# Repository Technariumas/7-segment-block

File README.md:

# 7-segment-block

A big 7 segment plug and play module designed to be easily chainable and be driven by SPI bus.

```Arduino
#include<SPI.h>
#include <Bounce2.h>

#define ZERO  0b11101110
#define ONE   0b10000010
#define TWO   0b11011100
#define THREE 0b11010110
#define FOUR  0b10110010
#define FIVE  0b01110110
#define SIX   0b01111110
#define SEVEN 0b11000010
#define EIGHT 0b11111110
#define NINE  0b11110110
#define DARK  0b00000000

uint8_t digits[] = {ZERO, ONE, TWO, THREE, FOUR, FIVE, SIX, SEVEN, EIGHT, NINE, DARK};
uint8_t brightness = 0;

void setup() {
  Serial.begin(9600);
  randomSeed(analogRead(0));
  
  //Output enable
  pinMode(6, OUTPUT);  
  digitalWrite(6, HIGH);
 
  //Latch
  pinMode(10, OUTPUT);
  digitalWrite(10, HIGH);
 
  //MOSI
  pinMode(11, OUTPUT);
  
  //SCK
  pinMode(13, OUTPUT);

  SPI.begin();
  SPI.setDataMode(SPI_MODE0);
  digitalWrite(6, LOW);  
}

void displayDigit(uint8_t digit1) {
    digitalWrite(10, LOW);
    SPI.transfer(digit1);
    digitalWrite(10, HIGH);  
}

uint8_t i = 0;

void loop() {
  displayDigit(digits[i]);
  i++;
  if(i > 9) {
    i = 0; 
  }
  while(brightness++ < 254) {
    analogWrite(6, brightness++);
    delay(10);   
  }
  brightness = 0;
  delay(10);
}

```

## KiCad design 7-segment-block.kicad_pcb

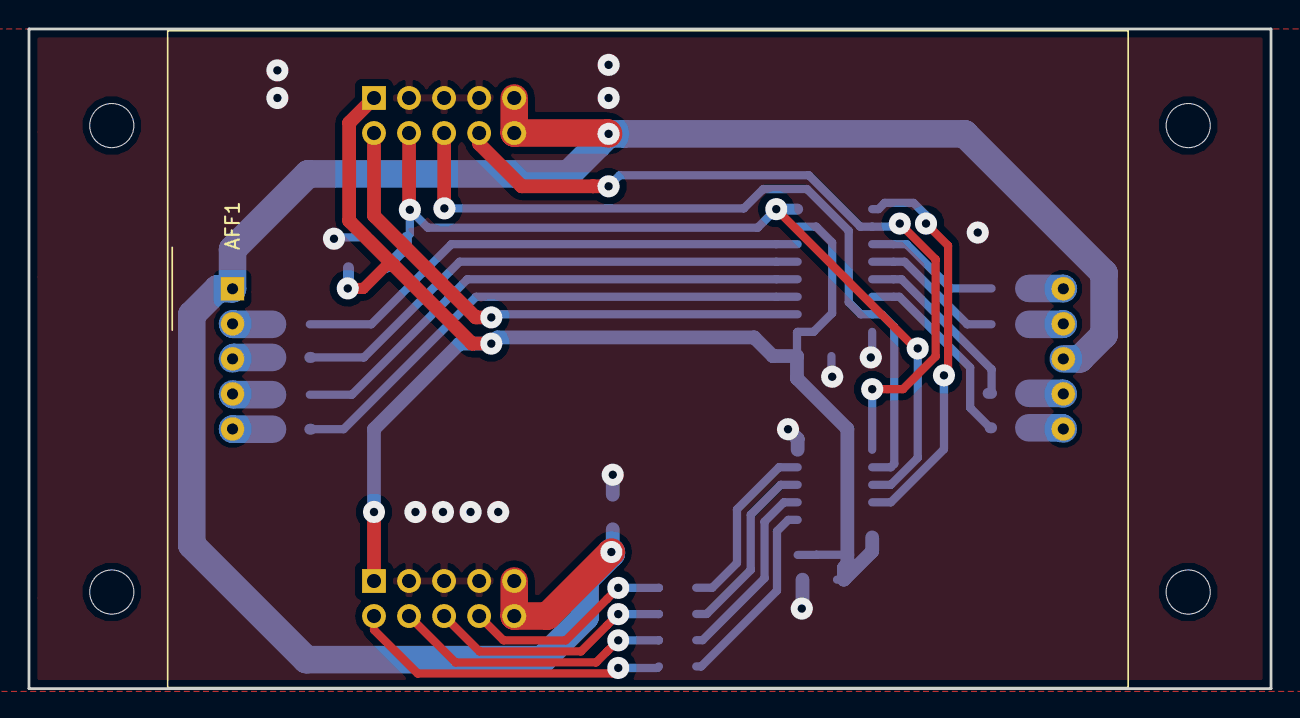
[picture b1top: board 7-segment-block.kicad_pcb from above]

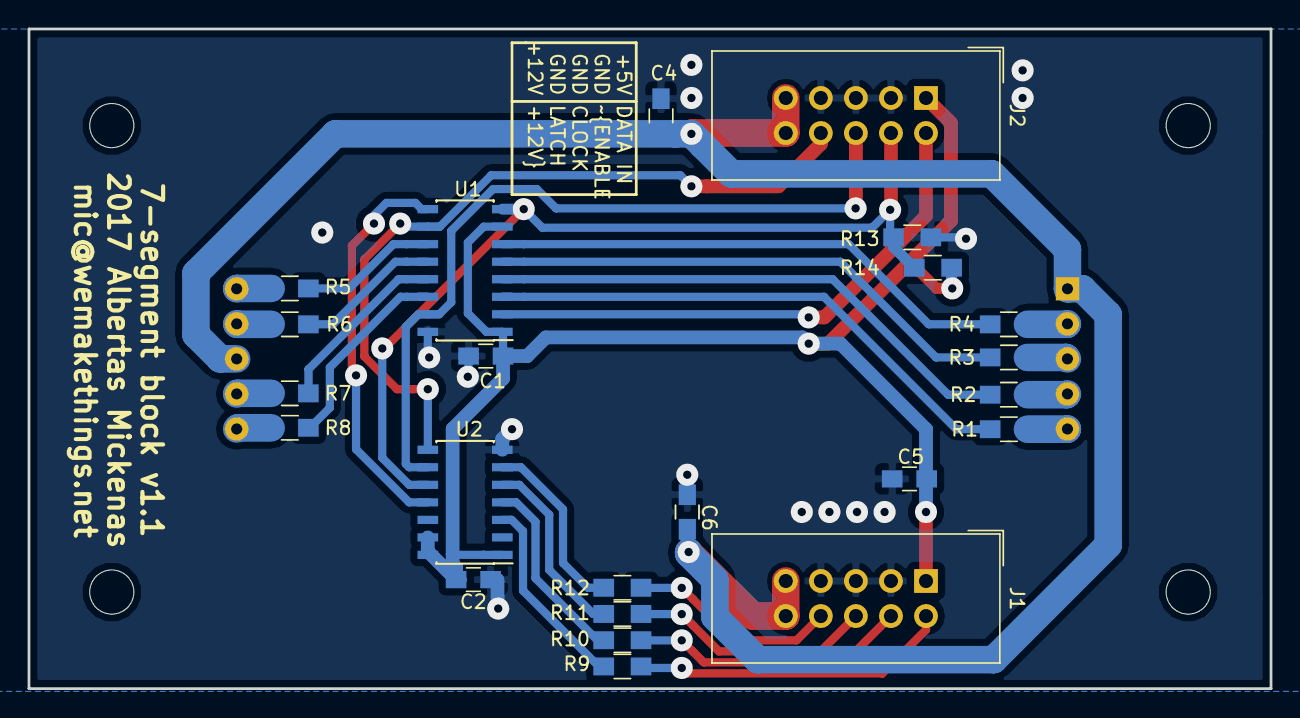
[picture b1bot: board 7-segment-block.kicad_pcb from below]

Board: 2 copper layers, 90.0 x 47.8 mm, 28 parts (23 on the bottom side), 32 nets.

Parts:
AFF1: OPD-S23010LE; SBC18-11SURKCGKWA
C1, C2, C4, C5, C6: C; C_0805_HandSoldering
J1: DATA_OUT; IDC-Header_2x05_Pitch2.54mm_Straight
J2: DATA_IN; IDC-Header_2x05_Pitch2.54mm_Straight
MK1, MK2, MK3, MK4: Mounting_Hole; MountingHole_3.2mm_M3
R1: 90; R_0805_HandSoldering
R2, R3, R4, R5, R6, R7, R8: 180; R_0805_HandSoldering
R9, R10, R11, R12: 100; R_0805_HandSoldering
R13, R14: 10k; R_0805_HandSoldering
U1: TPIC6C596PWR; SOIC-16_3.9x9.9mm_Pitch1.27mm
U2: 74LS243; SOIC-14_3.9x8.7mm_Pitch1.27mm

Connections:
+5V: C1.1, C2.1, C5.1, J1.1, J2.1, R14.2, U1.1, U1.7, U2.1, U2.13, U2.14
/RCK: J2.8, U1.10, U2.8
/SEG_A: AFF1.7, R7.1
/SEG_B: AFF1.6, R8.1
/SEG_C: AFF1.4, R2.1
/SEG_D: AFF1.3, R3.1
/SEG_DP: AFF1.5, R1.1
/SEG_E: AFF1.2, R4.1
/SEG_F: AFF1.9, R6.1
/SEG_G: AFF1.10, R5.1
/SER_IN: J2.2, U1.2
/SER_OUT: U1.9, U2.11
/SRCK: J2.6, U1.15, U2.9
/~G: J2.4, R13.1, R14.1, U1.8, U2.10
GND: C1.2, C2.2, C4.2, C5.2, C6.2, J1.3, J1.5, J1.7, J2.3, J2.5, J2.7, R13.2, U1.16, U2.7
unnamed: J1.2, R9.2
unnamed: J1.4, R10.2
unnamed: J1.6, R11.2
unnamed: J1.8, R12.2
unnamed: R1.2, U1.3
unnamed: R2.2, U1.4
unnamed: R3.2, U1.5
unnamed: R4.2, U1.6
unnamed: R5.2, U1.11
unnamed: R6.2, U1.12
unnamed: R7.2, U1.13
unnamed: R8.2, U1.14
unnamed: R9.1, U2.3
unnamed: R10.1, U2.4
unnamed: R11.1, U2.5
unnamed: R12.1, U2.6
VCC: AFF1.1, AFF1.8, C4.1, C6.1, J1.9, J1.10, J2.9, J2.10

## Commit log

2017-11-19 Start schematics, start PCB
2017-11-19 Add mounting holes, dropper resistors and a buffer
2017-11-19 Add terminator resistors
2017-11-19 Start routing, maybe change to a different buffer that has a more friendly pin location
2017-11-20 Finish routing, change buffer IC, add some decoupling caps
2017-11-20 Change orientation of cap to mitigate bendring problems. Add dimensions and hole markers
2017-12-24 Add pullup on ~G, send for manufacturing
2017-12-24 Add some lincence notices
2018-01-23 Add new pics and tune up the readme
2018-01-23 Remove dead code from example in README

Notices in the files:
7-segment-block.kicad_pcb:
Copyright 2017 Albertas Mickėnas
Licensed under the Apache License, Version 2.0 (the \"License\");
